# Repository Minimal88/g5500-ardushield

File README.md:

# G5500-ardushield
An arduino shield for controlling a Yaesu G5000 rotator.

## Intro
This is a simple Arduino Shield (compatible for any Duemilenove or Uno like boards) for controlling a Yaesu G5500 Antenna rotator.

This shield is designed to be used with K3NG Rotator controller software (flashed on arduino) which you can find [here](https://github.com/k3ng/k3ng_rotator_controller).
For the specific configuration please have a look on the branch maintained for this [here](https://github.com/ppapadeas/k3ng_rotator_controller/tree/lsf-g5500).

## Instructions

You have a couple of different options for producing this shield:
* Download the release file for off-the-shelf gerber files for local production.
* Or order the board directly from [OSHPark](https://oshpark.com/shared_projects/pu8Rst2N)
* Or download the sourcefiles from the repo and adjust them to your needs

Once you have a board ready make sure to flash the board with the K3NG software, properly configured for the pins assigned to each function.

You can see some pictures of the board homebrewed [here](https://goo.gl/photos/bw671UsoGTs3t2yWA).

## Contribute

Please open a github issue for any suggestions or bugs you find.

## License

This work is released under ﻿CERN Open Hardware Licence v1.2
Copyright 2016 Libre Space Foundation

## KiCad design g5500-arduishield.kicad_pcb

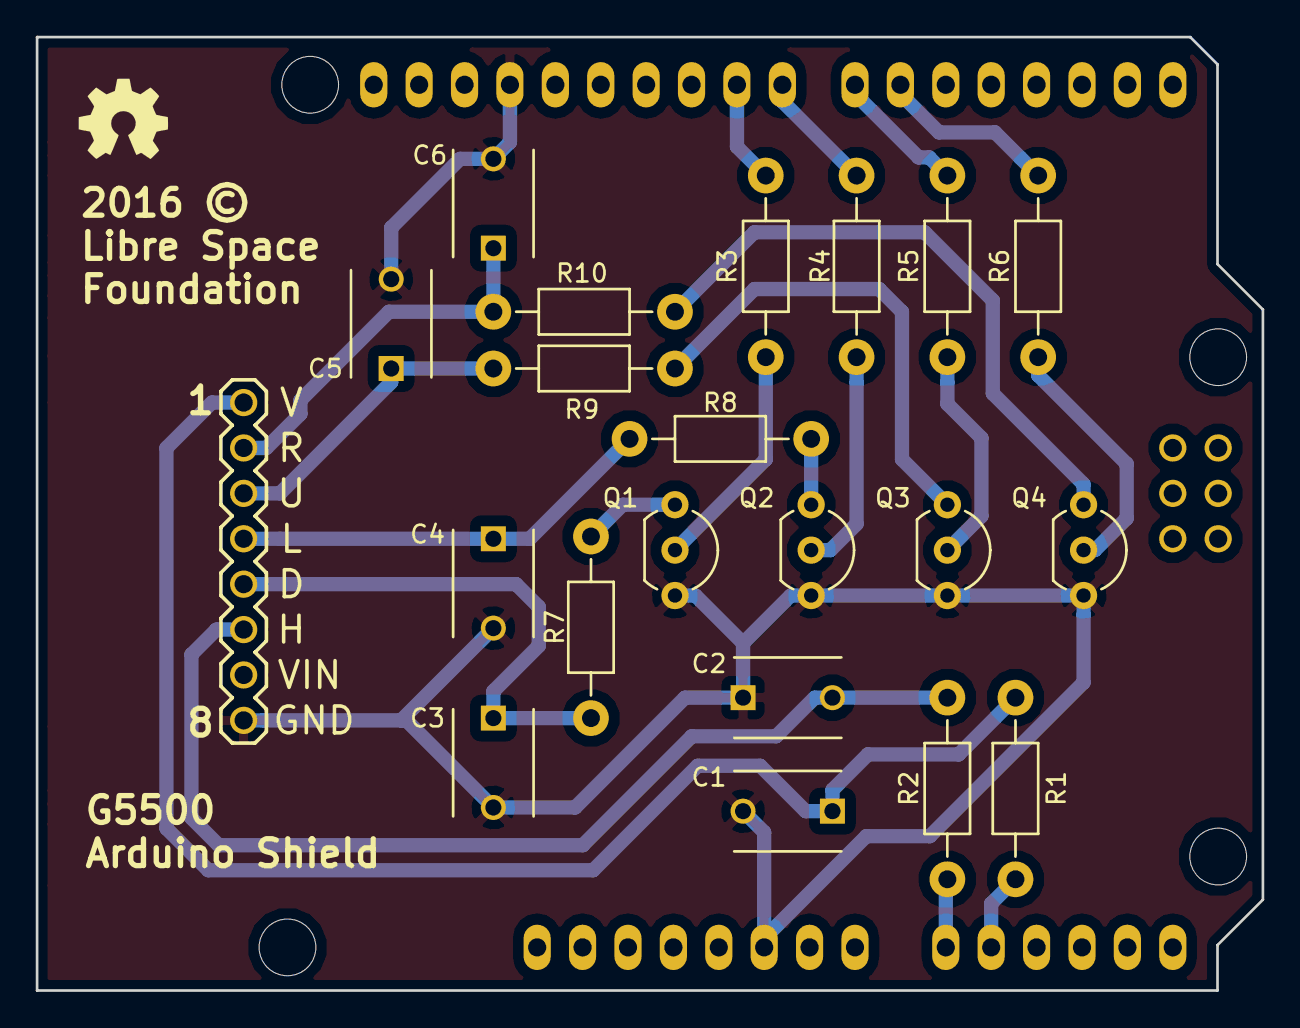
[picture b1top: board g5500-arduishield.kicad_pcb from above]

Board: 2 copper layers, 68.6 x 53.3 mm, 23 parts (0 on the bottom side), 21 nets.

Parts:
C1, C2, C3, C4, C5, C6: 10n; C_Disc_D6_P5
JP1: M08; 1X08
LOGO_OSHW_silkscreen_5mm: val**; LOGO_OSHW_silkscreen_5mm
Q1, Q2, Q3, Q4: PN2222A; TO-92_Inline_Wide
R1, R2, R3, R4, R5, R6: 1K; Resistor_Horizontal_RM10mm
R7, R8, R9, R10: 33K; Resistor_Horizontal_RM10mm
SHIELD1: ARDUINO_SHIELD

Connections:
D: C3.1, JP1.5, R7.1
GND: C1.2, C2.1, C3.2, C4.2, C5.2, C6.2, JP1.8, Q1.3, Q2.3, Q3.3, Q4.3, SHIELD1.GND1, SHIELD1.GND3
H: C1.1, JP1.1, R1.1
L: C4.1, JP1.4, R8.1
unnamed: Q1.1, R7.2
unnamed: Q1.2, R3.1
unnamed: Q2.1, R8.2
unnamed: Q2.2, R4.1
unnamed: Q3.1, R9.2
unnamed: Q3.2, R5.1
unnamed: Q4.1, R10.2
unnamed: Q4.2, R6.1
unnamed: R1.2, SHIELD1.AD1
unnamed: R2.2, SHIELD1.AD0
unnamed: R3.2, SHIELD1.9
unnamed: R4.2, SHIELD1.8
unnamed: R5.2, SHIELD1.7
unnamed: R6.2, SHIELD1.6
R: C6.1, JP1.2, R10.1
U: C5.1, JP1.3, R9.1
V: C2.2, JP1.6, R2.1

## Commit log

2016-01-01 First take on controller shield
2016-01-01 Added license
2016-01-01 Added pictures link
2016-10-30 Updated with new configuration.
2017-02-28 Add gerber files
2017-05-04 Add slight routing adjustments and addition of F.Cu GND zone
